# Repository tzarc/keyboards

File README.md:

# @tzarc's Keyboards.

Here you'll find the design files for @tzarc's custom keyboard designs.

Since February 2024, licenses have changed from GPL3 to CERN-OHL-S.

## Djinn

The [Djinn](Djinn/README.md) is a 64-key split keyboard -- dual 4x7 with a 4-key thumb cluster. It also has a 5-way tactile switch under the thumb.

## Ghoul

The [Ghoul](Ghoul/README.md) is a Planck-like development board for QMK, using SparkFun MicroMod for hot-swap MCU capability in a `2x4x5=40` layout with encoder and RGB OLED, per-key RGB.

## Kobold

The [Kobold](Kobold/README.md) is an ortho 4x4 macropad, as a replacement for a bm16s with modern hardware.

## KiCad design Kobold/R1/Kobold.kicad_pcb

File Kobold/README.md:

# Kobold

4x4 macropad running QMK, in the same form factor as a bm16s. Non-standard Choc key spacing.

STM32G431, North-facing RGB, SPI NOR Flash, voltage and current measurement, direct pin matrix, reset to bootloader by holding top 4 keys.

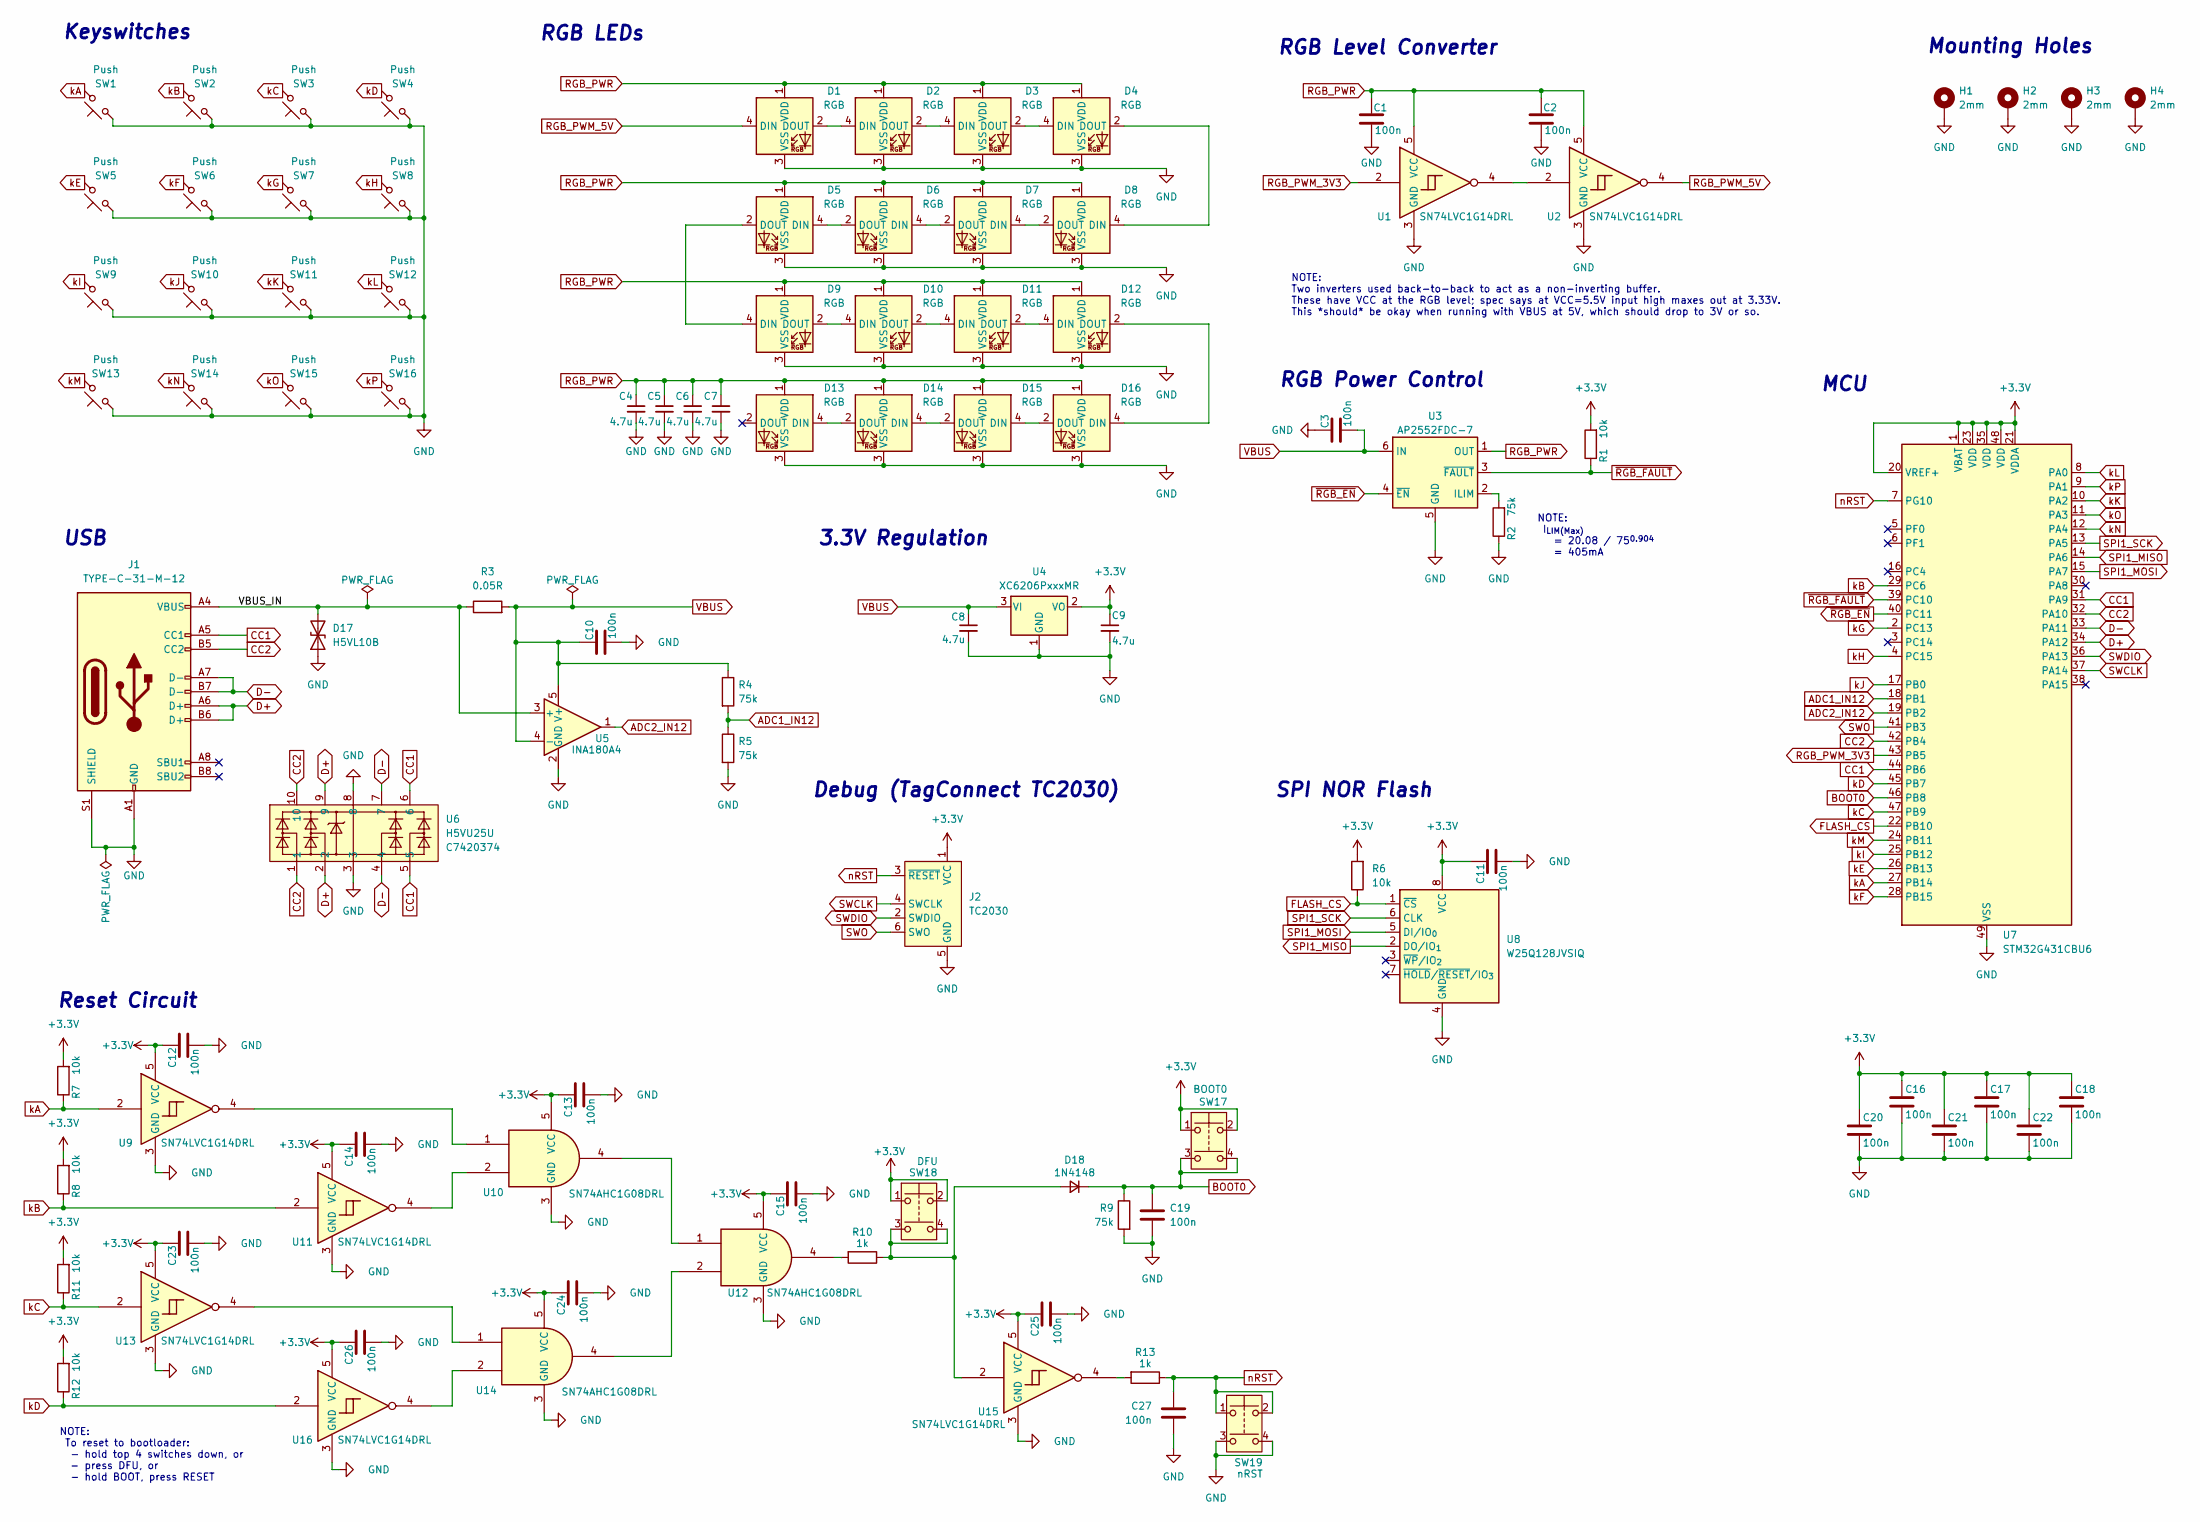
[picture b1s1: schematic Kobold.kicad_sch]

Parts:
C1, C2, C3, C10, C11, C12, C13, C14, C15, C16, C17, C18, C19, C20, C21, C22, C23, C24, C25, C26, C27: 100n; C_0402_1005Metric; LCSC C1525
C4, C5, C6, C7, C8, C9: 4.7u; C_0402_1005Metric; LCSC C23733
D1, D2, D3, D4, D9, D10, D11, D12: RGB; LED_choc_6028R; LCSC C5149201
D5, D6, D7, D8, D13, D14, D15, D16: RGB; LED_choc_6028R-ROT; LCSC C5149201
D17: H5VL10B; D_SOD-882; LCSC C7420372
D18: 1N4148; D_SOD-323; LCSC C2128
H1, H2, H3, H4: 2mm; MountingHole_2.2mm_M2_Pad
J1: TYPE-C-31-M-12; USB_C_Receptacle_HRO_TYPE-C-31-M-12; LCSC C165948
J2: TC2030; Tag-Connect_TC2030-IDC-FP_2x03_P1.27mm_Vertical
R1, R6, R7, R8, R11, R12: 10k; R_0402_1005Metric; LCSC C25744
R2, R4, R5, R9: 75k; R_0603_1608Metric; LCSC C23242
R3: 0.05R; R_1206_3216Metric; LCSC C912768
R10, R13: 1k; R_0402_1005Metric; LCSC C11702
SW1, SW2, SW3, SW4, SW5, SW6, SW7, SW8, SW9, SW10, SW11, SW12, SW13, SW14, SW15, SW16: Push; SW_choc_v1_HS_CPG135001S30_1u
SW17: BOOT0; SW-SMD_4P-L3.0-W2.6-P1.80-LS3.4-TL; LCSC C778132
SW18: DFU; SW-SMD_4P-L3.0-W2.6-P1.80-LS3.4-TL; LCSC C778132
SW19: nRST; SW-SMD_4P-L3.0-W2.6-P1.80-LS3.4-TL; LCSC C778132
U1, U2, U9, U11, U13, U15, U16: SN74LVC1G14DRL; SOT-553-5_L1.6-W1.2-P0.50-LS1.6-BL; LCSC C2682052
U3: AP2552FDC-7; WDFN-6_L2.0-W2.0-P0.65-BL-EP-1; LCSC C150475
U4: XC6206PxxxMR; SOT-23-3; LCSC C5446
U5: INA180A4; SOT-23-5_L3.0-W1.7-P0.95-LS2.8-BR; LCSC C188337
U6: H5VU25U; DFN2510-10_L2.5-W1.0-P0.50-BL; LCSC C7420374
U7: STM32G431CBU6; QFN-48-1EP_7x7mm_P0.5mm_EP5.6x5.6mm; LCSC C529356
U8: W25Q128JVSIQ; SOIC-8_5.3x5.3mm_P1.27mm; LCSC C97521
U10, U12, U14: SN74AHC1G08DRL; SOT-553-5_L1.6-W1.2-P0.50-LS1.6-BL; LCSC C352951

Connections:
+3.3V: C9.1, C11.1, C12.1, C13.1, C14.1, C15.1, C16.1, C17.1, C18.1, C20.1, C21.1, C22.1, C23.1, C24.1, C25.1, C26.1, J2.1 (VCC), R1.2, R6.2, R7.2, R8.2, R11.2, R12.2, SW17.1, SW17.2, SW18.1, SW18.2, U4.2 (VO), U7.1 (VBAT), U7.20 (VREF+), U7.21 (VDDA), U7.23 (VDD), U7.35 (VDD), U7.48 (VDD), U8.8 (VCC), U9.5 (VCC), U10.5 (VCC), U11.5 (VCC), U12.5 (VCC), U13.5 (VCC), U14.5 (VCC), U15.5 (VCC), U16.5 (VCC)
/VBUS_IN: D17.2 (A2), J1.A4 (VBUS), J1.A9 (VBUS), J1.B4 (VBUS), J1.B9 (VBUS), R3.1, U5.3 (+)
ADC1_IN12: R4.2, R5.1, U7.18 (PB1)
ADC2_IN12: U5.1, U7.19 (PB2)
BOOT0: C19.1, D18.1 (K), R9.1, SW17.3, SW17.4, U7.46 (PB8)
CC1: J1.A5 (CC1), U6.5, U6.6, U7.31 (PA9), U7.44 (PB6)
CC2: J1.B5 (CC2), U6.1, U6.10, U7.32 (PA10), U7.42 (PB4)
D+: J1.A6 (D+), J1.B6 (D+), U6.2, U6.9, U7.34 (PA12)
D-: J1.A7 (D-), J1.B7 (D-), U6.4, U6.7, U7.33 (PA11)
FLASH_CS: R6.1, U7.22 (PB10), U8.1 (~CS)
GND: C1.2, C2.2, C3.1, C4.2, C5.2, C6.2, C7.2, C8.2, C9.2, C10.2, C11.2, C12.2, C13.2, C14.2, C15.2, C16.2, C17.2, C18.2, C19.2, C20.2, C21.2, C22.2, C23.2, C24.2, C25.2, C26.2, C27.2, D1.3 (VSS), D2.3 (VSS), D3.3 (VSS), D4.3 (VSS), D5.3 (VSS), D6.3 (VSS), D7.3 (VSS), D8.3 (VSS), D9.3 (VSS), D10.3 (VSS), D11.3 (VSS), D12.3 (VSS), D13.3 (VSS), D14.3 (VSS), D15.3 (VSS), D16.3 (VSS), D17.1 (A1), H1.1, H2.1, H3.1, H4.1, J1.A1 (GND), J1.A12 (GND), J1.B1 (GND), J1.B12 (GND), J1.S1 (SHIELD), J2.5 (GND), R2.1, R5.2, R9.2, SW1.1, SW2.1, SW3.1, SW4.1, SW5.1, SW6.1, SW7.1, SW8.1, SW9.1, SW10.1, SW11.1, SW12.1, SW13.1, SW14.1, SW15.1, SW16.1, SW19.3, SW19.4, U1.3 (GND), U2.3 (GND), U3.5 (GND), U3.7 (EP), U4.1 (GND), U5.2 (GND), U6.3, U6.8, U7.49 (VSS), U8.4 (GND), U9.3 (GND), U10.3 (GND), U11.3 (GND), U12.3 (GND), U13.3 (GND), U14.3 (GND), U15.3 (GND), U16.3 (GND)
unnamed: D1.2 (DOUT), D2.4 (DIN)
unnamed: D2.2 (DOUT), D3.4 (DIN)
unnamed: D3.2 (DOUT), D4.4 (DIN)
unnamed: D4.2 (DOUT), D8.4 (DIN)
unnamed: D5.4 (DIN), D6.2 (DOUT)
unnamed: D5.2 (DOUT), D9.4 (DIN)
unnamed: D6.4 (DIN), D7.2 (DOUT)
unnamed: D7.4 (DIN), D8.2 (DOUT)
unnamed: D9.2 (DOUT), D10.4 (DIN)
unnamed: D10.2 (DOUT), D11.4 (DIN)
unnamed: D11.2 (DOUT), D12.4 (DIN)
unnamed: D12.2 (DOUT), D16.4 (DIN)
unnamed: D13.4 (DIN), D14.2 (DOUT)
unnamed: D14.4 (DIN), D15.2 (DOUT)
unnamed: D15.4 (DIN), D16.2 (DOUT)
unnamed: D18.2 (A), R10.1, SW18.3, SW18.4, U15.2
unnamed: R10.2, U12.4
unnamed: R13.2, U15.4
unnamed: U1.4, U2.2
unnamed: R2.2, U3.2 (ILIM)
unnamed: U9.4, U10.1
unnamed: U10.2, U11.4
unnamed: U10.4, U12.1
unnamed: U12.2, U14.4
unnamed: U13.4, U14.1
unnamed: U14.2, U16.4
RGB_PWM_3V3: U1.2, U7.43 (PB5)
RGB_PWM_5V: D1.4 (DIN), U2.4
RGB_PWR: C1.1, C2.1, C4.1, C5.1, C6.1, C7.1, D1.1 (VDD), D2.1 (VDD), D3.1 (VDD), D4.1 (VDD), D5.1 (VDD), D6.1 (VDD), D7.1 (VDD), D8.1 (VDD), D9.1 (VDD), D10.1 (VDD), D11.1 (VDD), D12.1 (VDD), D13.1 (VDD), D14.1 (VDD), D15.1 (VDD), D16.1 (VDD), U1.5 (VCC), U2.5 (VCC), U3.1 (OUT)
SPI1_MISO: U7.14 (PA6), U8.2 (DO/IO_{1})
SPI1_MOSI: U7.15 (PA7), U8.5 (DI/IO_{0})
SPI1_SCK: U7.13 (PA5), U8.6 (CLK)
SWCLK: J2.4 (SWCLK), U7.37 (PA14)
SWDIO: J2.2 (SWDIO), U7.36 (PA13)
SWO: J2.6 (SWO), U7.41 (PB3)
VBUS: C3.2, C8.1, C10.1, R3.2, R4.1, U3.6 (IN), U4.3 (VI), U5.4 (-), U5.5 (V+)
kA: R7.1, SW1.2, U7.27 (PB14), U9.2
kB: R8.1, SW2.2, U7.29 (PC6), U11.2
kC: R11.1, SW3.2, U7.47 (PB9), U13.2
kD: R12.1, SW4.2, U7.45 (PB7), U16.2
kE: SW5.2, U7.26 (PB13)
kF: SW6.2, U7.28 (PB15)
kG: SW7.2, U7.2 (PC13)
kH: SW8.2, U7.4 (PC15)
kI: SW9.2, U7.25 (PB12)
kJ: SW10.2, U7.17 (PB0)
kK: SW11.2, U7.10 (PA2)
kL: SW12.2, U7.8 (PA0)
kM: SW13.2, U7.24 (PB11)
kN: SW14.2, U7.12 (PA4)
kO: SW15.2, U7.11 (PA3)
kP: SW16.2, U7.9 (PA1)
nRST: C27.1, J2.3 (~RESET), R13.1, SW19.1, SW19.2, U7.7 (PG10)
~RGB_EN: U3.4 (~EN), U7.40 (PC11)
~RGB_FAULT: R1.1, U3.3 (~FAULT), U7.39 (PC10)

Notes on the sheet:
NOTE: I_{LIM(Max)} = 20.08 / 75^{0.904} = 405mA
SPI NOR Flash
Reset Circuit
MCU
RGB Power Control
3.3V Regulation
RGB Level Converter
RGB LEDs
Mounting Holes
USB
NOTE: To reset to bootloader: - hold top 4 switches down, or - press DFU, or - hold BOOT, press RESET
Keyswitches
Debug (TagConnect TC2030)
NOTE: Two inverters used back-to-back to act as a non-inverting buffer. These have VCC at the RGB level; spec says at VCC=5.5V input high maxes out at 3.33V. This *should* be okay when running with VBUS at 5V, which should drop to 3V or so.

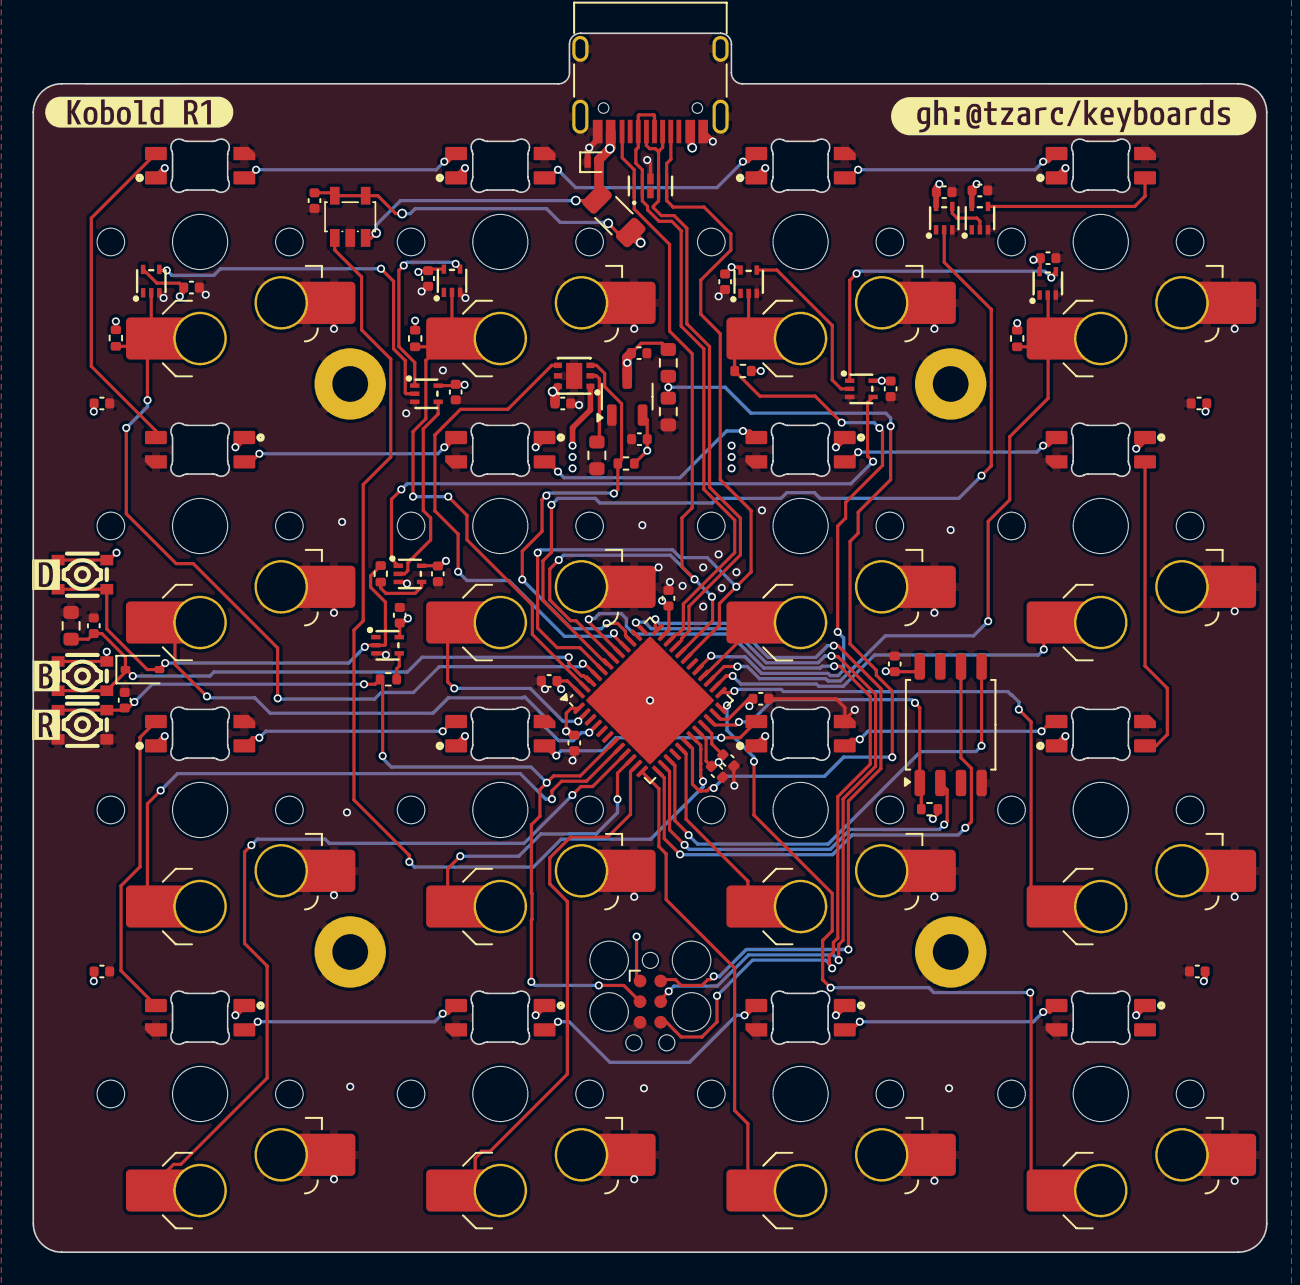
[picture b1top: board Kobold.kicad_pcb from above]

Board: 4 copper layers, 76.0 x 75.1 mm, 104 parts (0 on the bottom side), 66 nets.

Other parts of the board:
kibuzzard-677E65CD: G***; kibuzzard-677E65CD
kibuzzard-677E65D8: G***; kibuzzard-677E65D8
kibuzzard-677E65DF: G***; kibuzzard-677E65DF
kibuzzard-677E6627: G***; kibuzzard-677E6627
kibuzzard-677E6634: G***; kibuzzard-677E6634

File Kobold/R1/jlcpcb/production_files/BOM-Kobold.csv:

Comment,Designator,Footprint,LCSC,Quantity
1k,"R10,R13",R_0402_1005Metric,C11702,2
AP2552FDC-7,U3,WDFN-6_L2.0-W2.0-P0.65-BL-EP-1,C150475,1
100n,"C1,C10,C11,C12,C13,C14,C15,C16,C17,C18,C19,C2,C20,C21,C22,C23,C24,C25,C26,C27,C3",C_0402_1005Metric,C1525,21
TYPE-C-31-M-12,J1,USB_C_Receptacle_HRO_TYPE-C-31-M-12,C165948,1
INA180A4,U5,SOT-23-5_L3.0-W1.7-P0.95-LS2.8-BR,C188337,1
1N4148,D18,D_SOD-323,C2128,1
75k,"R2,R4,R5,R9",R_0603_1608Metric,C23242,4
4.7u,"C4,C5,C6,C7,C8,C9",C_0402_1005Metric,C23733,6
10k,"R1,R11,R12,R6,R7,R8",R_0402_1005Metric,C25744,6
SN74LVC1G14DRL,"U1,U11,U13,U15,U16,U2,U9",SOT-553-5_L1.6-W1.2-P0.50-LS1.6-BL,C2682052,7
SN74AHC1G08DRL,"U10,U12,U14",SOT-553-5_L1.6-W1.2-P0.50-LS1.6-BL,C352951,3
RGB,"D1,D10,D11,D12,D13,D14,D15,D16,D2,D3,D4,D5,D6,D7,D8,D9",LED_choc_6028R,C5149201,16
STM32G431CBU6,U7,QFN-48-1EP_7x7mm_P0.5mm_EP5.6x5.6mm,C529356,1
XC6206PxxxMR,U4,SOT-23-3,C5446,1
H5VL10B,D17,D_SOD-882,C7420372,1
H5VU25U,U6,DFN2510-10_L2.5-W1.0-P0.50-BL,C7420374,1
BOOT0,"SW17,SW18,SW19",SW-SMD_4P-L3.0-W2.6-P1.80-LS3.4-TL,C778132,3
0.05R,R3,R_1206_3216Metric,C912768,1
W25Q128JVSIQ,U8,SOIC-8_5.3x5.3mm_P1.27mm,C97521,1
Push,SW14,SW_choc_v1_HS_CPG135001S30_1u,,1
Push,SW11,SW_choc_v1_HS_CPG135001S30_1u,,1
Push,SW13,SW_choc_v1_HS_CPG135001S30_1u,,1
Push,SW5,SW_choc_v1_HS_CPG135001S30_1u,,1
Push,SW10,SW_choc_v1_HS_CPG135001S30_1u,,1
Push,SW16,SW_choc_v1_HS_CPG135001S30_1u,,1
Push,SW6,SW_choc_v1_HS_CPG135001S30_1u,,1
Push,SW7,SW_choc_v1_HS_CPG135001S30_1u,,1
Push,SW12,SW_choc_v1_HS_CPG135001S30_1u,,1
Push,SW2,SW_choc_v1_HS_CPG135001S30_1u,,1
Push,SW8,SW_choc_v1_HS_CPG135001S30_1u,,1
Push,SW4,SW_choc_v1_HS_CPG135001S30_1u,,1
Push,SW15,SW_choc_v1_HS_CPG135001S30_1u,,1
Push,SW9,SW_choc_v1_HS_CPG135001S30_1u,,1
Push,SW3,SW_choc_v1_HS_CPG135001S30_1u,,1
Push,SW1,SW_choc_v1_HS_CPG135001S30_1u,,1

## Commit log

2020-10-22 Rev1.
2020-10-22 Readme.
2020-10-22 Links to code.
2020-10-25 Add Rev1 BOM document.
2020-10-25 Missed the link to the knob.
2020-10-25 Add fasteners to the BOM.
2020-10-25 Added some notes to the BOM.
2020-12-02 Modified readme to point to the generated djinn qmk_firmware branch.
2020-12-05 Add info about deficiencies with rev1.
2021-04-11 Add Rev2a.
2021-04-11 Glamour shots of Rev2a.
2021-04-11 Generate some more DXF's.
2021-04-12 Add note about JLC randomly charging extra.
2021-04-27 Add alternative parts.
2021-05-09 Add DXF warning.
2021-05-12 Add STLs for Rev2a.
2021-05-18 New image.
2021-05-27 Fixup BOM -- add LCD, fixup F931C107KCC 100uF cap.
2021-09-09 Add first batch troubleshooting docs.
2021-11-23 Alternate ESD protection diode.
2022-06-20 Djinn is now on QMK `master`.
2024-02-17 Consolidate keyboards into a single repository.
2025-04-04 Initial commit of Kobold.
2025-04-16 Add Kobold.
